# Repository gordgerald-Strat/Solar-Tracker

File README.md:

# Solar-Tracker
A dual-axis hardware solar tracker utilizing microcontrollers,  phototransistors, and custom firmware to maximize solar panel energy efficiency.

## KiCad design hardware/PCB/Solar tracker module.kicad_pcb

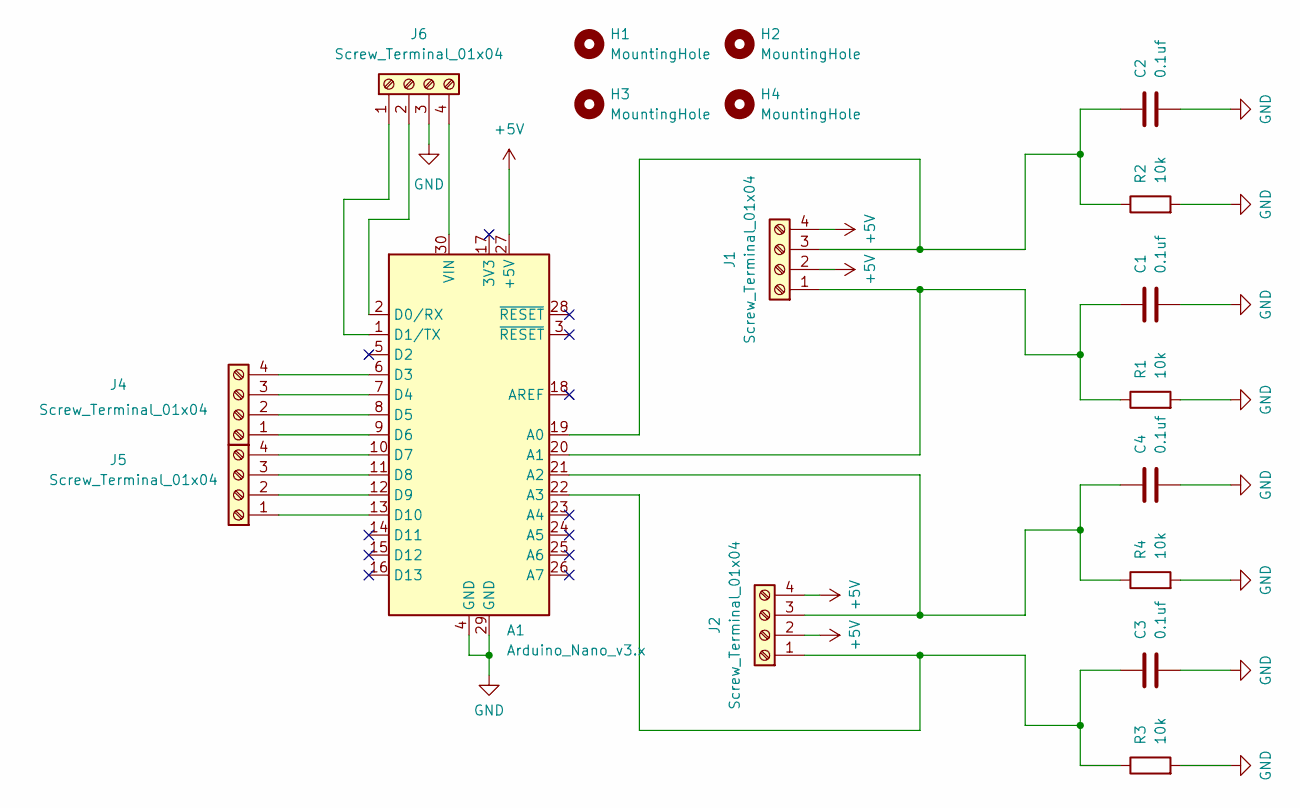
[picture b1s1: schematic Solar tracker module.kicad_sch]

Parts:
A1: Arduino_Nano_v3.x; Arduino_Nano
C1, C2, C3, C4: 0.1uf; C_Disc_D5.0mm_W2.5mm_P5.00mm
H1, H2, H3, H4: MountingHole; MountingHole_3.2mm_M3
J1, J2, J4, J5, J6: Screw_Terminal_01x04; TerminalBlock_Phoenix_PT-1,5-4-3.5-H_1x04_P3.50mm_Horizontal
R1, R2, R3, R4: 10k; R_Axial_DIN0207_L6.3mm_D2.5mm_P7.62mm_Horizontal

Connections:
+5V: A1.27 (+5V), J1.2, J1.4, J2.2, J2.4
GND: A1.4 (GND), A1.29 (GND), C1.2, C2.2, C3.2, C4.2, J6.3, R1.2, R2.2, R3.2, R4.2
unnamed: A1.19 (A0), C2.1, J1.3, R2.1
unnamed: A1.20 (A1), C1.1, J1.1, R1.1
unnamed: A1.21 (A2), C4.1, J2.3, R4.1
unnamed: A1.22 (A3), C3.1, J2.1, R3.1
unnamed: A1.2 (D0/RX), J6.2
unnamed: A1.1 (D1/TX), J6.1
unnamed: A1.6 (D3), J4.4
unnamed: A1.7 (D4), J4.3
unnamed: A1.8 (D5), J4.2
unnamed: A1.9 (D6), J4.1
unnamed: A1.10 (D7), J5.4
unnamed: A1.11 (D8), J5.3
unnamed: A1.12 (D9), J5.2
unnamed: A1.13 (D10), J5.1
unnamed: A1.30 (VIN), J6.4

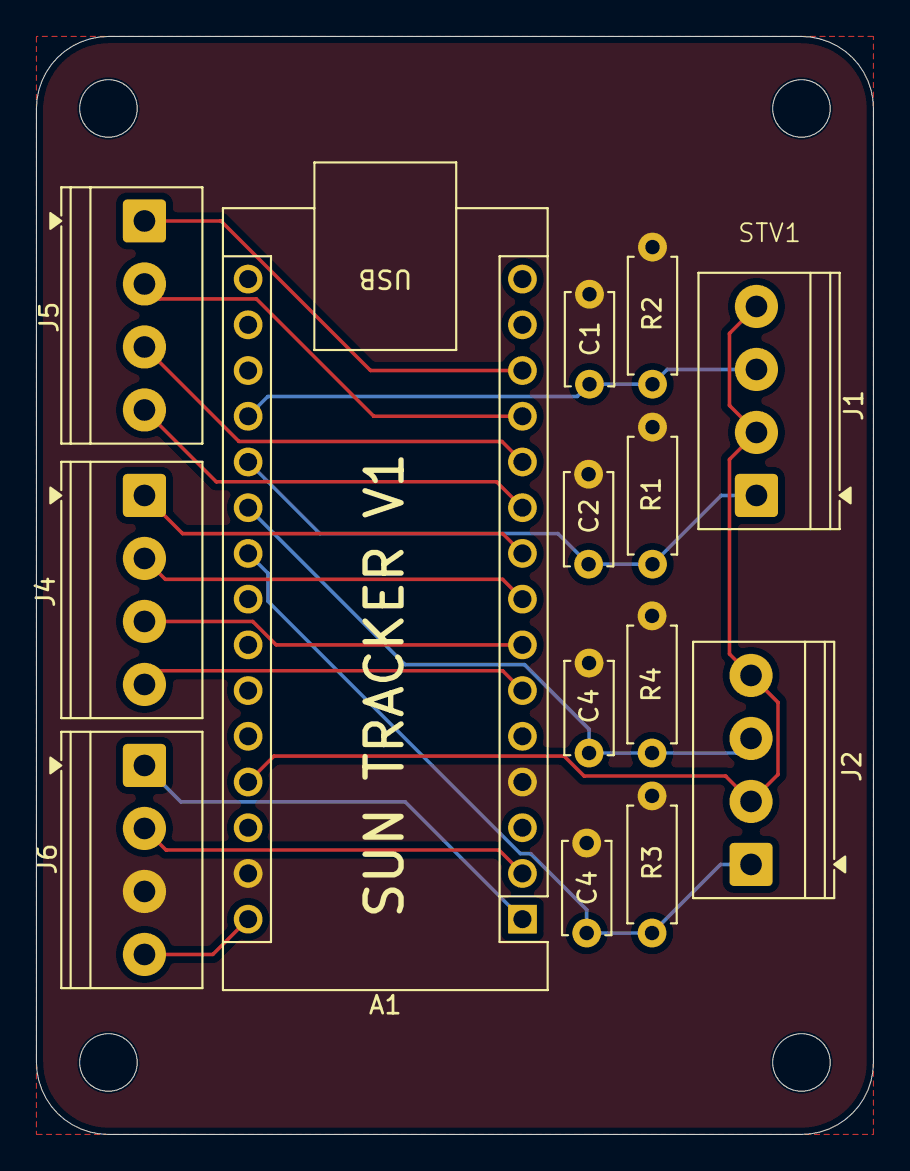
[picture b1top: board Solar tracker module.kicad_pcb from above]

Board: 2 copper layers, 46.5 x 61.0 mm, 18 parts (0 on the bottom side), 17 nets.
